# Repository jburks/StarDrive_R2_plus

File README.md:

# StarDrive_R2_plus
StarBoard SCSI Drive attachment with real-time clock

## Mini-FAQ:

### What is it?

StarDrive R2+ is an upgraded version of Chris "Crispy" Brenner's original reverse-engineered remake of the Microbotics StarDrive for their
StarBoard 2 expansion module for the Amiga 1000.

### Where can I get it?

This product is still in development. All files necessary for making your own will be here and links to assembled boards for sale will be
placed here when available.

### What's the status?

The original project has been converted to KiCAD and ports have been placed as accurately as possible using the materials still available
from Crispy's original design. Additional footprints for the slightly more available PCF8573T and footprints for a microcontroller and modern RTC are
WIP.

### What's this about an upgrade?

The original StarDrive uses two components that are no longer in production: the AM5380 SCSI interface controller; and the PCF8573P real-time clock.
Direct replacements are not known to be available for either, so StarBoard R2+ is planned to contain a microcontroller capable of emulating the PCF8573
so that a modern, easy to source solution is available. A substitute for the AM5380 has not been identified.

### How can I help?

The project would benefit from a modified StarBoard 2 driver that modifies the I2C code to talk to a modern RTC directly so that a PCF8573 or a
microcontroller that emulates one is not necessary.

## Board renderings

### Front:

### Back:

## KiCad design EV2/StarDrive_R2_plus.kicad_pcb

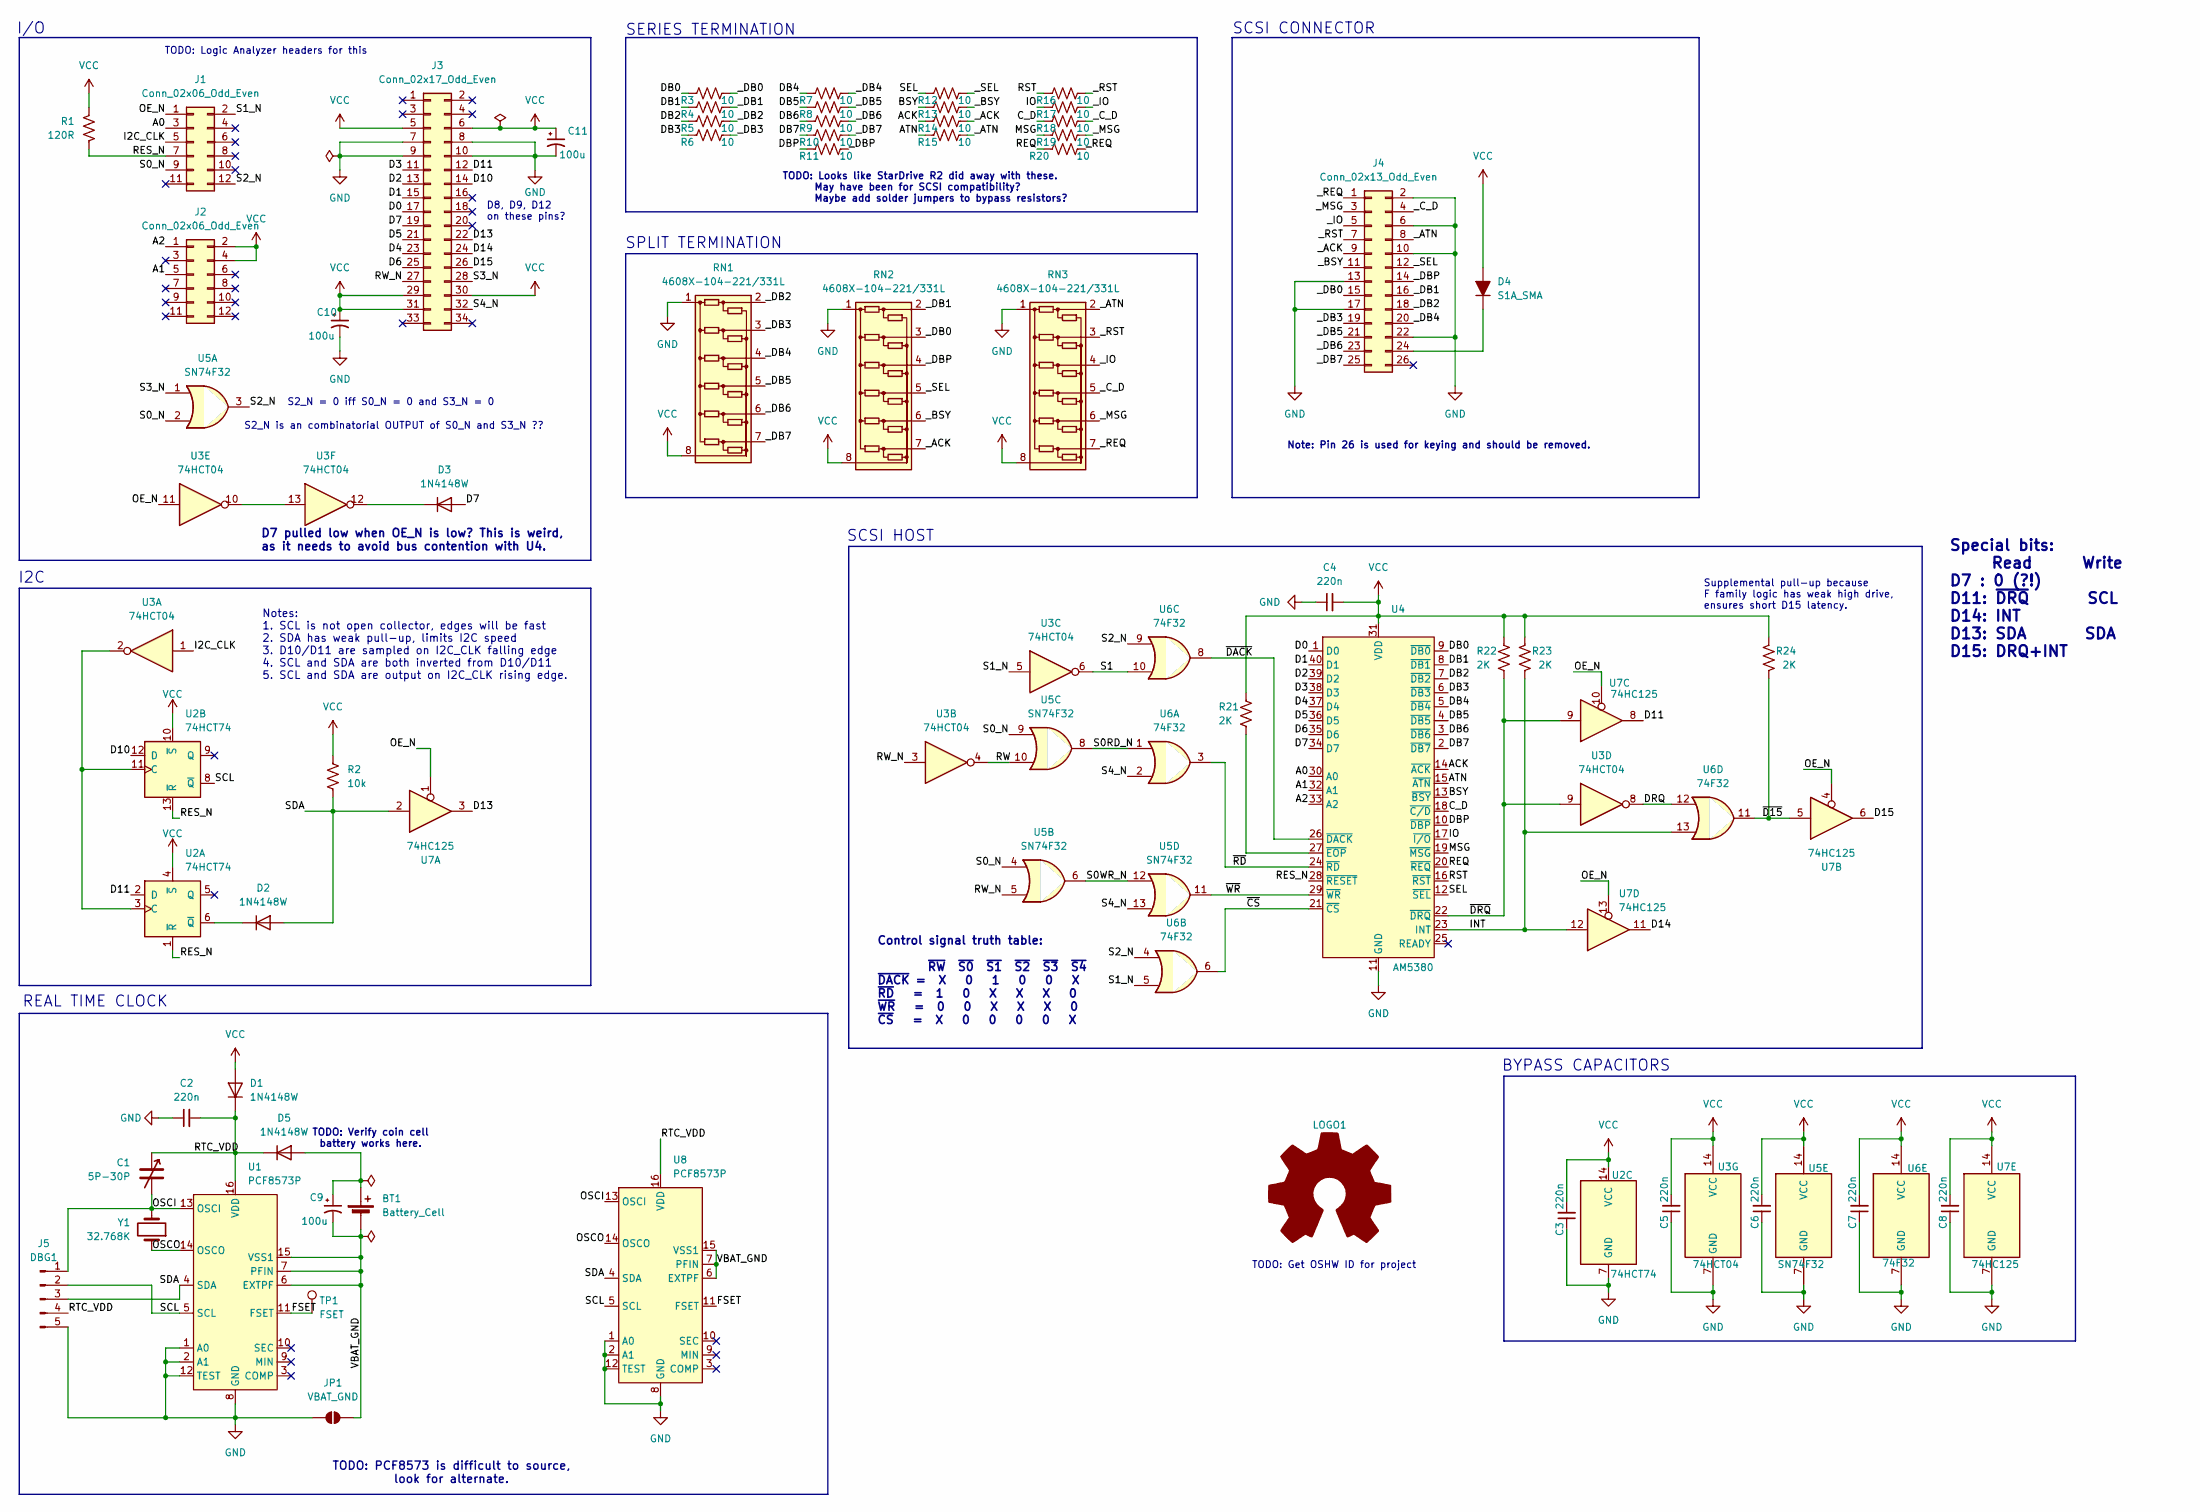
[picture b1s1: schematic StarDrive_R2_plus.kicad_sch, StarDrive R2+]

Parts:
BT1: Battery_Cell; AliEx_BatClip
C1: 5P-30P; C_Trimmer_Voltronics_JZ; Part JZ300
C2, C3, C4, C5, C6, C7, C8: 220n; C_0603_1608Metric_Pad1.08x0.95mm_HandSolder
C9, C10, C11: 100u; CP_EIA-6032-15_Kemet-U
D1, D2, D3, D5: 1N4148W; D_SOD-323_HandSoldering
D4: S1A_SMA; D_SMA
J1, J2: Conn_02x06_Odd_Even; PinSocket_2x06_P2.54mm_Vertical
J3: Conn_02x17_Odd_Even; PinSocket_2x17_P2.54mm_Vertical
J4: Conn_02x13_Odd_Even; PinHeader_2x13_P2.54mm_Vertical
J5: DBG1; PinHeader_1x05_P2.54mm_Vertical
JP1: VBAT_GND; SolderJumper-2_P1.3mm_Open_Pad1.0x1.5mm
LOGO1: Logo_Open_Hardware_Large; OSHW-Logo_11.4x12mm_SilkScreen
R1: 120R; R_0603_1608Metric_Pad0.98x0.95mm_HandSolder
R2: 10k; R_0603_1608Metric_Pad0.98x0.95mm_HandSolder
R3, R4, R5, R6, R7, R8, R9, R10, R11, R12, R13, R14, R15, R16, R17, R18, R19, R20: 10; R_0603_1608Metric_Pad0.98x0.95mm_HandSolder
R21, R22, R23, R24: 2K; R_0603_1608Metric_Pad0.98x0.95mm_HandSolder
RN1, RN2, RN3: 4608X-104-221/331L; R_Array_SIP8
TP1: FSET; TestPoint_Pad_D2.0mm
U1: PCF8573P; DIP-16_W7.62mm
U2: 74HCT74; SO-14_3.9x8.65mm_P1.27mm
U3: 74HCT04; SOIC-14_3.9x8.7mm_P1.27mm
U4: AM5380; DIP-40_W15.24mm
U5: SN74F32; SOIC-14_3.9x8.7mm_P1.27mm
U6: 74F32; SOIC-14_3.9x8.7mm_P1.27mm
U7: 74HC125; SOIC-14_3.9x8.7mm_P1.27mm
U8: PCF8573P; SOIC-16W_7.5x10.3mm_P1.27mm
Y1: 32.768K; Crystal_SMD_3215-2Pin_3.2x1.5mm; Part CC7V-T1A-32.768kHz-12.5pF-20PPM-TC-QC

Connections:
/A0: J1.3, U4.30 (A0)
/A1: J2.5, U4.32 (A1)
/A2: J2.1, U4.33 (A2)
/ACK: R14.1, U4.14 (~ACK)
/ATN: R15.1, U4.15 (~ATN)
/BSY: R13.1, U4.13 (~BSY)
/C_D: R18.1, U4.18 (~C/D)
/D0: J3.17, U4.1 (D0)
/D1: J3.15, U4.40 (D1)
/D2: J3.13, U4.39 (D2)
/D3: J3.11, U4.38 (D3)
/D4: J3.23, U4.37 (D4)
/D5: J3.21, U4.36 (D5)
/D6: J3.25, U4.35 (D6)
/D7: D3.2 (A), J3.19, U4.34 (D7)
/D10: J3.14, U2.12 (D)
/D11: J3.12, U2.2 (D), U7.8
/D13: J3.22, U7.3
/D14: J3.24, U7.11
/D15: J3.26, U7.6
/DB0: R3.1, U4.9 (~DB0)
/DB1: R4.1, U4.8 (~DB1)
/DB2: R5.1, U4.7 (~DB2)
/DB3: R6.1, U4.6 (~DB3)
/DB4: R7.1, U4.5 (~DB4)
/DB5: R8.1, U4.4 (~DB5)
/DB6: R9.1, U4.3 (~DB6)
/DB7: R10.1, U4.2 (~DB7)
/DBP: R11.1, U4.10 (~DBP)
/DRQ: U3.8, U6.12
/FSET: TP1.1, U1.11 (FSET), U8.11 (FSET)
/I2C_CLK: J1.5, U3.1
/INT: R23.2, U4.23 (INT), U6.13, U7.12
/IO: R17.1, U4.17 (~I/O)
/MSG: R19.1, U4.19 (~MSG)
/OE_N: J1.1, U3.11, U7.1, U7.4, U7.10, U7.13
/OSCI: C1.2, J5.1, U1.13 (OSCI), U8.13 (OSCI), Y1.2
/OSCO: U1.14 (OSCO), U8.14 (OSCO), Y1.1
/REQ: R20.1, U4.20 (~REQ)
/RES_N: J1.7, R1.1, U2.1 (~R), U2.13 (~R), U4.28 (~RESET)
/RST: R16.1, U4.16 (~RST)
/RTC_VDD: C1.1, C2.2, D1.1 (K), D5.1 (K), J5.4, U1.16 (VDD), U8.16 (VDD)
/RW: U3.4, U5.10
/RW_N: J3.27, U3.3, U5.5
/S0RD_N: U5.8, U6.1
/S0WR_N: U5.6, U5.12
/S0_N: J1.9, U5.2, U5.4, U5.9
/S1: U3.6, U6.10
/S1_N: J1.2, U3.5, U6.5
/S2_N: J1.12, U5.3, U6.4, U6.9
/S3_N: J3.28, U5.1
/S4_N: J3.32, U5.13, U6.2
/SCL: J5.2, U1.5 (SCL), U2.8 (~Q), U8.5 (SCL)
/SDA: D2.2 (A), J5.3, R2.2, U1.4 (SDA), U7.2, U8.4 (SDA)
/SEL: R12.1, U4.12 (~SEL)
/VBAT_GND: BT1.2 (-), C9.2, JP1.2 (B), U1.6 (EXTPF), U1.7 (PFIN), U1.15 (VSS1), U8.6 (EXTPF), U8.7 (PFIN), U8.15 (VSS1)
/_ACK: J4.9, R14.2, RN2.7 (R6)
/_ATN: J4.8, R15.2, RN3.2 (R1)
/_BSY: J4.11, R13.2, RN2.6 (R5)
/_C_D: J4.4, R18.2, RN3.5 (R4)
/_DB0: J4.15, R3.2, RN2.3 (R2)
/_DB1: J4.16, R4.2, RN2.2 (R1)
/_DB2: J4.18, R5.2, RN1.2 (R1)
/_DB3: J4.19, R6.2, RN1.3 (R2)
/_DB4: J4.20, R7.2, RN1.4 (R3)
/_DB5: J4.21, R8.2, RN1.5 (R4)
/_DB6: J4.23, R9.2, RN1.6 (R5)
/_DB7: J4.25, R10.2, RN1.7 (R6)
/_DBP: J4.14, R11.2, RN2.4 (R3)
/_IO: J4.5, R17.2, RN3.4 (R3)
/_MSG: J4.3, R19.2, RN3.6 (R5)
/_REQ: J4.1, R20.2, RN3.7 (R6)
/_RST: J4.7, R16.2, RN3.3 (R2)
/_SEL: J4.12, R12.2, RN2.5 (R4)
/~CS: U4.21 (~CS), U6.6
/~D15: R24.2, U6.11, U7.5
/~DACK: U4.26 (~DACK), U6.8
/~DRQ: R22.2, U3.9, U4.22 (~DRQ), U7.9
/~RD: U4.24 (~RD), U6.3
/~WR: U4.29 (~WR), U5.11
GND: C2.1, C3.1, C4.1, C5.1, C6.1, C7.1, C8.1, C10.2, C11.2, J3.7, J3.8, J3.9, J3.10, J4.2, J4.6, J4.10, J4.13, J4.17, J4.22, J5.5, JP1.1 (A), RN1.1 (COM1), RN2.1 (COM1), RN3.1 (COM1), U1.1 (A0), U1.2 (A1), U1.8 (GND), U1.12 (TEST), U2.7 (GND), U3.7 (GND), U4.11 (GND), U5.7 (GND), U6.7 (GND), U7.7 (GND), U8.1 (A0), U8.2 (A1), U8.8 (GND), U8.12 (TEST)
unnamed: BT1.1 (+), C9.1, D5.2 (A)
unnamed: D2.1 (K), U2.6 (~Q)
unnamed: D3.1 (K), U3.12
unnamed: D4.1 (K), J4.24
unnamed: U2.3 (C), U2.11 (C), U3.2
unnamed: U3.10, U3.13
unnamed: R21.2, U4.27 (~EOP)
VCC: C3.2, C4.2, C5.2, C6.2, C7.2, C8.2, C10.1, C11.1, D1.2 (A), D4.2 (A), J2.2, J2.4, J3.5, J3.6, J3.29, J3.30, J3.31, R1.2, R2.1, R21.1, R22.1, R23.1, R24.1, RN1.8 (COM2), RN2.8 (COM2), RN3.8 (COM2), U2.4 (~S), U2.10 (~S), U2.14 (VCC), U3.14 (VCC), U4.31 (VDD), U5.14 (VCC), U6.14 (VCC), U7.14 (VCC)

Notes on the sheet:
TODO: Verify coin cell battery works here.
I/O
TODO: Get OSHW ID for project
D7 pulled low when OE_N is low? This is weird, as it needs to avoid bus contention with U4.
Special bits: Read Write D7 : 0 (?!) D11: ~{DRQ} SCL D14: INT D13: SDA SDA D15: DRQ+INT
BYPASS CAPACITORS
S2_N = 0 iff S0_N = 0 and S3_N = 0
REAL TIME CLOCK
SCSI HOST
TODO: Logic Analyzer headers for this
Supplemental pull-up because F family logic has weak high drive, ensures short D15 latency.
D8, D9, D12 on these pins?
I2C
TODO: PCF8573 is difficult to source, look for alternate.
Control signal truth table: ~{RW} ~{S0} ~{S1} ~{S2} ~{S3} ~{S4} ~{DACK} = X 0 1 0 0 X ~{RD} = 1 0 X X X 0 ~{WR} = 0 0 X X X 0 ~{CS} = X 0 0 0 0 X
SCSI CONNECTOR
SPLIT TERMINATION
Note: Pin 26 is used for keying and should be removed.
SERIES TERMINATION
TODO: Looks like StarDrive R2 did away with these. May have been for SCSI compatibility? Maybe add solder jumpers to bypass resistors?
Notes: 1. SCL is not open collector, edges will be fast 2. SDA has weak pull-up, limits I2C speed 3. D10/D11 are sampled on I2C_CLK falling edge 4. SCL and SDA are both inverted from D10/D11 5. SCL and SDA are output on I2C_CLK rising edge.
S2_N is an combinatorial OUTPUT of S0_N and S3_N ??

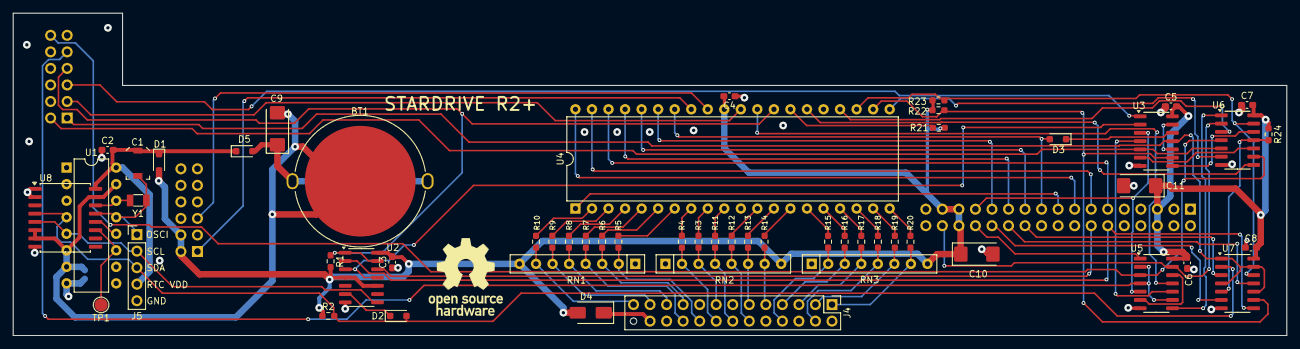
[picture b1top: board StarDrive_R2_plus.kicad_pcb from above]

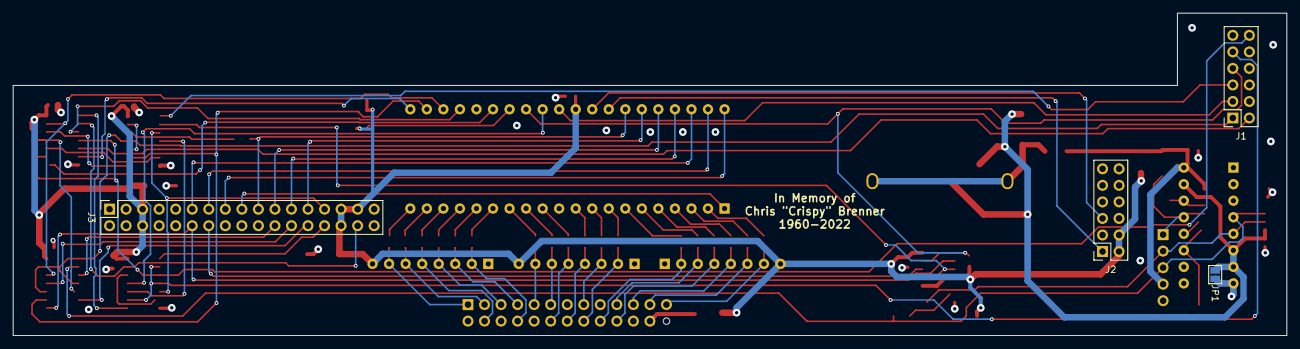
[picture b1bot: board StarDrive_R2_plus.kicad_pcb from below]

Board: 4 copper layers, 195.6 x 49.5 mm, 61 parts (4 on the bottom side), 89 nets.

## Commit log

2025-02-25 Initial EV1 commit
2025-02-25 Added notes and comments to schematic Added schematic plot
2025-03-28 Updated header locations
2025-03-28 Add renderings
2025-08-21 First prototype Gerber out
2025-08-21 Add missing files
2025-11-05 Create EV2 folder
2025-11-05 Fix #3 #4
2025-11-06 Remove SMD resistor arrays with individual resistors and switch to hand-solder footprints.
